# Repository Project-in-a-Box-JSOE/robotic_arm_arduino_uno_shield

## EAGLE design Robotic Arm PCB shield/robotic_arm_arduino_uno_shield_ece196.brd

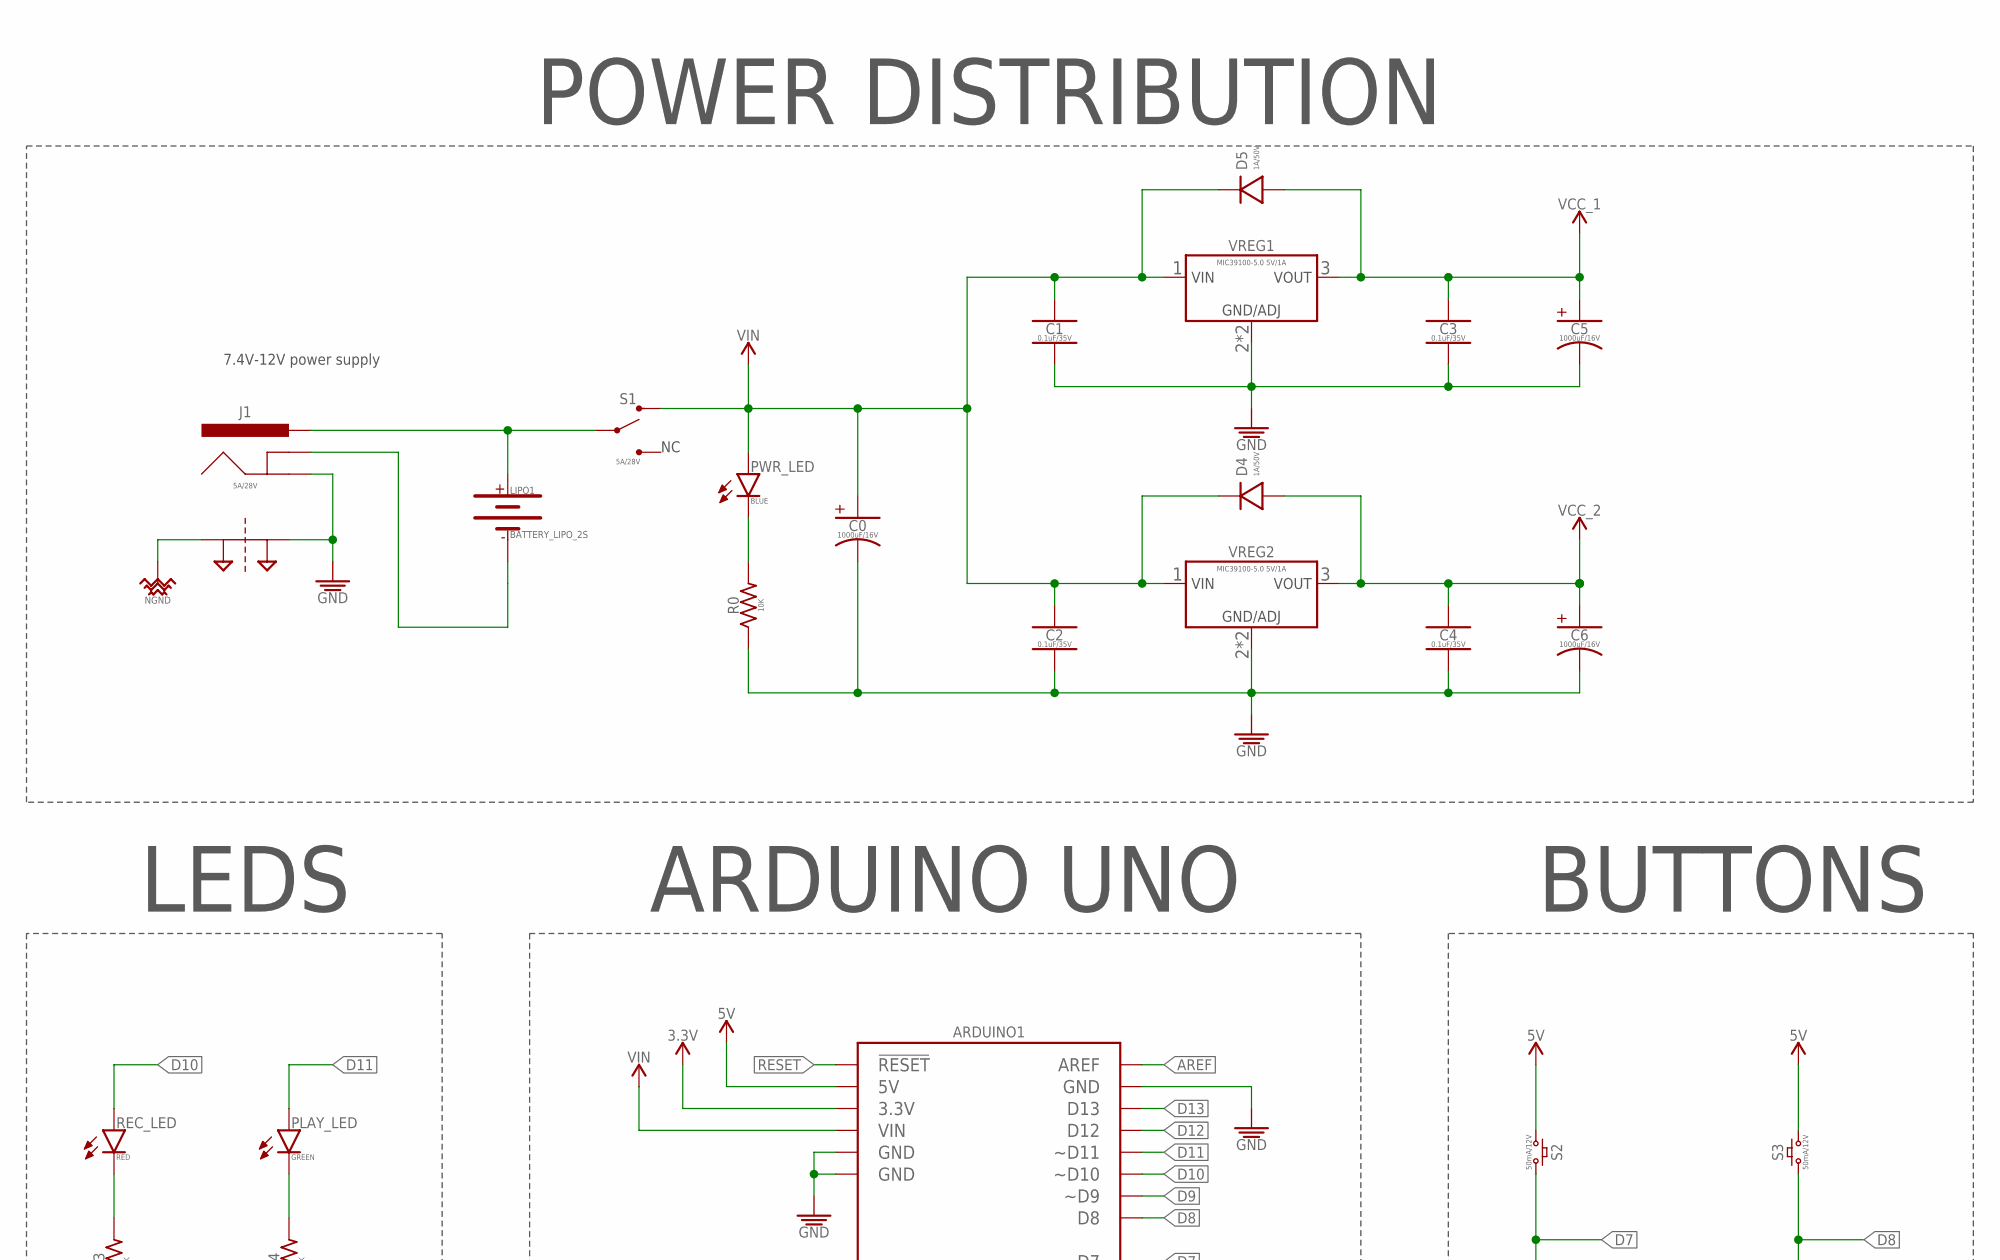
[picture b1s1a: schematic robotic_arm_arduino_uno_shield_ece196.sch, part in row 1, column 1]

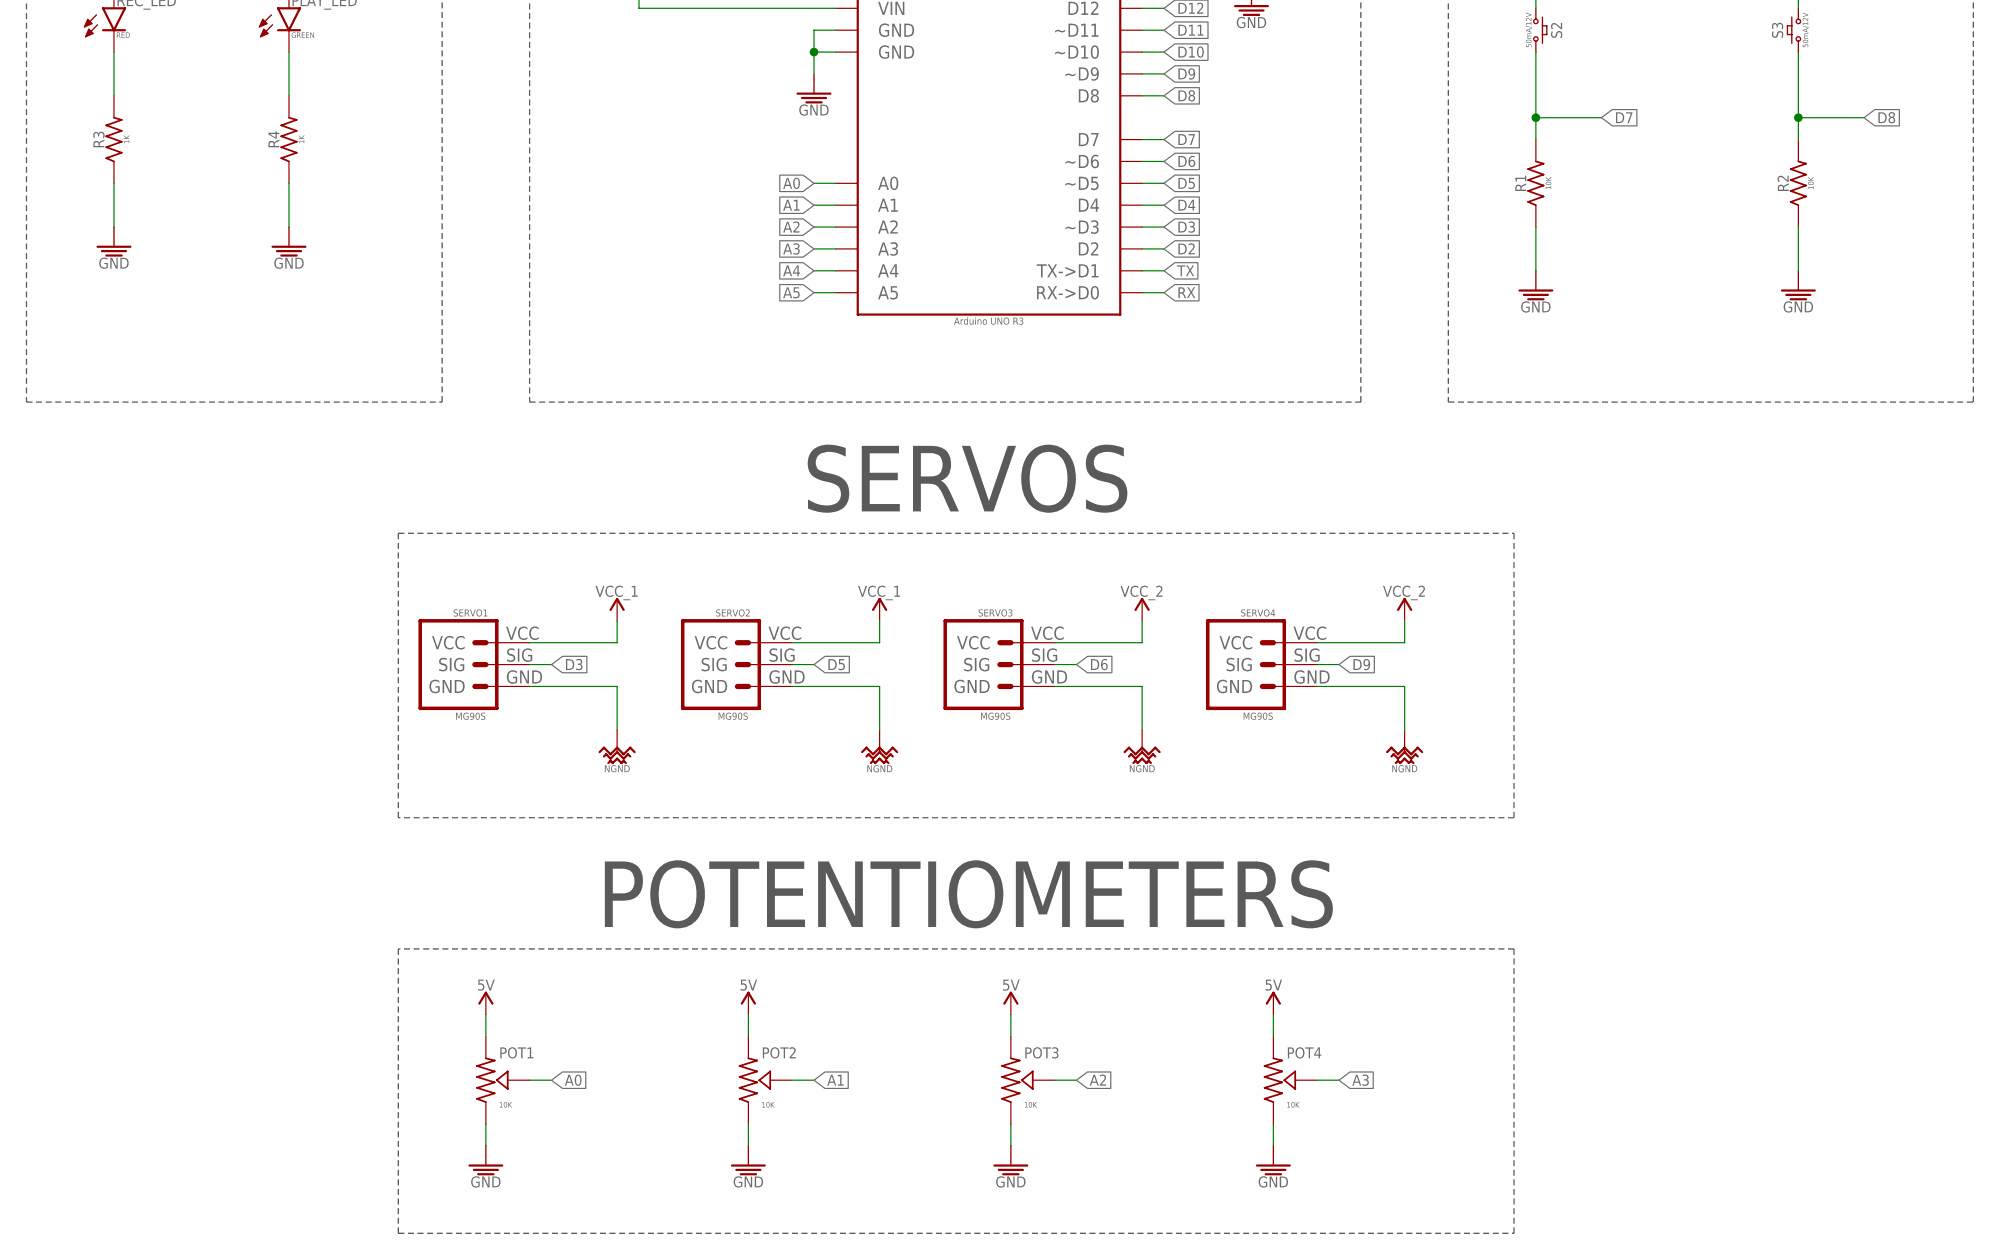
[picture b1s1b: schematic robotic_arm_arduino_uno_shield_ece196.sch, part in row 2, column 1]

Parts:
ARDUINO1: Arduino UNO R3; ARDUINO_UNO_R3_NO-HOLES_NO-AVR-ISP_NO-I2C_NO-NC_NO-IOREF
C0, C5, C6: 1000uF/16V; _AE_PTH_DIA8-LS3.5-H21.50
C1, C2, C3, C4: 0.1uF/35V; CAPC2012X95_SMD-0805
D4, D5: 1A/50V; SODFL3516X170
J1: 5A/28V; POWER_JACK_PTH_ID2.1MM-OD5.5MM
LIPO1: BATTERY_LIPO_2S; DUAL_PTH_PADS
PLAY_LED: GREEN; LEDC2012X120_LED-0805
POT1, POT2, POT3, POT4: 10K; HDRVR3W64P254_1X3_812X254X850B
PWR_LED: BLUE; LEDC2012X120_LED-0805
R0, R1, R2: 10K; RESC2012X60_SMD-0805
R3, R4: 1K; RESC2012X60_SMD-0805
REC_LED: RED; LEDC2012X120_LED-0805
S1: 5A/28V; SW_TOGGLE_SPDT_5A-28V_13L-7W
S2, S3: 50mA/12V; BTN_MOMENTARY_SPST-NO_PTH_L12-W12
SERVO1, SERVO2, SERVO3, SERVO4: MG90S; HDRVR3W64P254_1X3_812X254X850B
SUPPLY14: NET_BRIDGE
VREG1, VREG2: MIC39100-5.0 5V/1A; SOT229P700X180-4

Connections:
3.3V: ARDUINO1.3.3V
5V: ARDUINO1.5V, POT1.CCW, POT2.CCW, POT3.CCW, POT4.CCW, S2.1, S3.3 (2)
+: J1.PWR, LIPO1.+, S1.P
-: J1.GND_BATTERY, LIPO1.-
A0: ARDUINO1.A0, POT1.S
A1: ARDUINO1.A1, POT2.S
A2: ARDUINO1.A2, POT3.S
A3: ARDUINO1.A3, POT4.S
A4: ARDUINO1.A4
A5: ARDUINO1.A5
AREF: ARDUINO1.AREF
D2: ARDUINO1.D2
D3: ARDUINO1.D3 (~D3), SERVO1.SIG
D4: ARDUINO1.D4
D5: ARDUINO1.D5 (~D5), SERVO2.SIG
D6: ARDUINO1.D6 (~D6), SERVO3.SIG
D7: ARDUINO1.D7, R1.2, S2.3 (2)
D8: ARDUINO1.D8, R2.2, S3.1
D9: ARDUINO1.D9 (~D9), SERVO4.SIG
D10: ARDUINO1.D10 (~D10), REC_LED.A
D11: ARDUINO1.D11 (~D11), PLAY_LED.A
D12: ARDUINO1.D12
D13: ARDUINO1.D13
GND: ARDUINO1.GND@1 (GND), ARDUINO1.GND@2 (GND), ARDUINO1.GND@3 (GND), C0.- (K), C1.2, C2.2, C3.2, C4.2, C5.- (K), C6.- (K), J1.GND_JACK, POT1.CW, POT2.CW, POT3.CW, POT4.CW, R0.1, R1.1, R2.1, R3.1, R4.1, SUPPLY14.P$2, VREG1.2 (GND), VREG1.TAB (GND), VREG2.2 (GND), VREG2.TAB (GND)
unnamed: PLAY_LED.K, R4.2
unnamed: R3.2, REC_LED.K
unnamed: PWR_LED.K, R0.2
NGND: SERVO1.GND, SERVO2.GND, SERVO3.GND, SERVO4.GND, SUPPLY14.P$1
RESET: ARDUINO1.RESET@1 (!RESET!)
RX: ARDUINO1.D0 (RX->D0)
TX: ARDUINO1.D1 (TX->D1)
VCC_1: C3.1, C5.+ (A), D5.A, SERVO1.VCC, SERVO2.VCC, VREG1.3 (VO)
VCC_2: C4.1, C6.+ (A), D4.A, SERVO3.VCC, SERVO4.VCC, VREG2.3 (VO)
VIN: ARDUINO1.VIN, C0.+ (A), C1.1, C2.1, D4.K, D5.K, PWR_LED.A, S1.S1, VREG1.1 (VI), VREG2.1 (VI)

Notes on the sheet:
7.4V-12V power supply
SERVOS
LEDS
BUTTONS
ARDUINO UNO
POTENTIOMETERS
POWER DISTRIBUTION

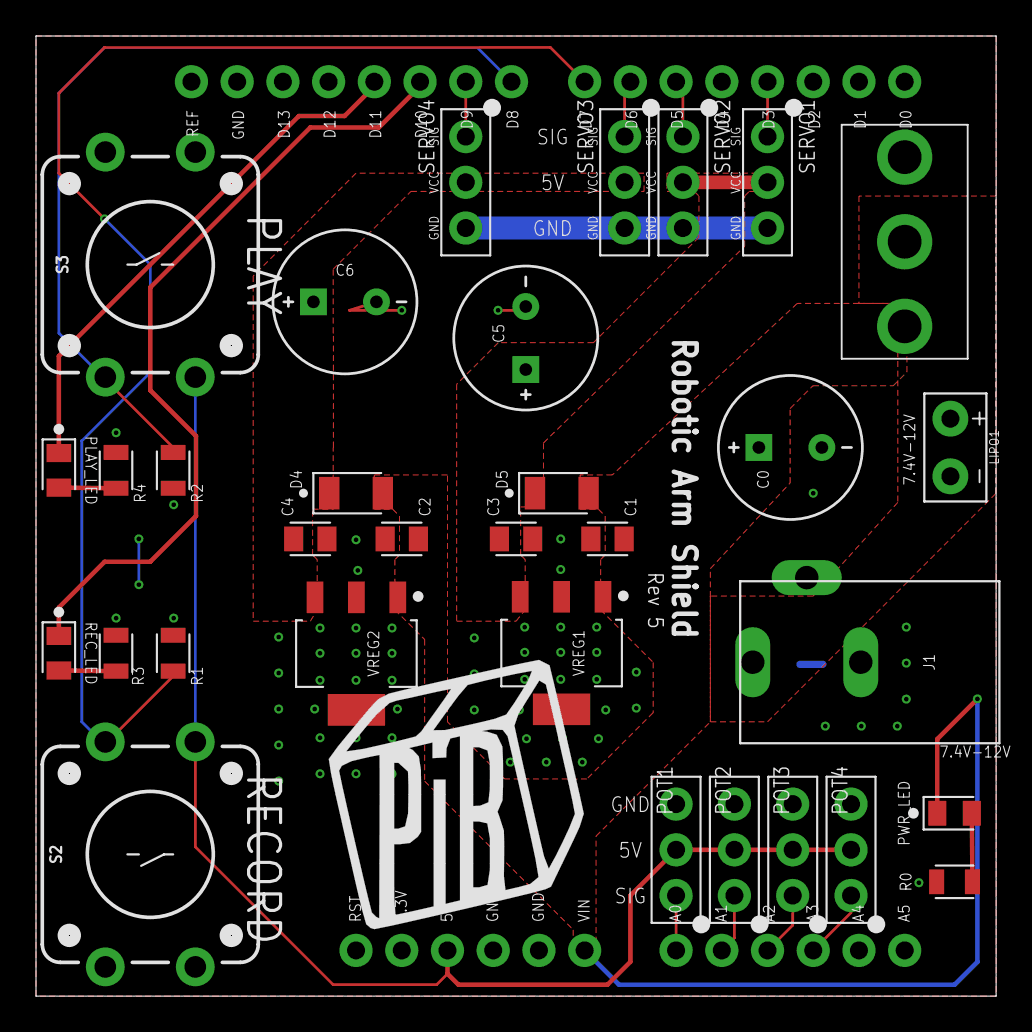
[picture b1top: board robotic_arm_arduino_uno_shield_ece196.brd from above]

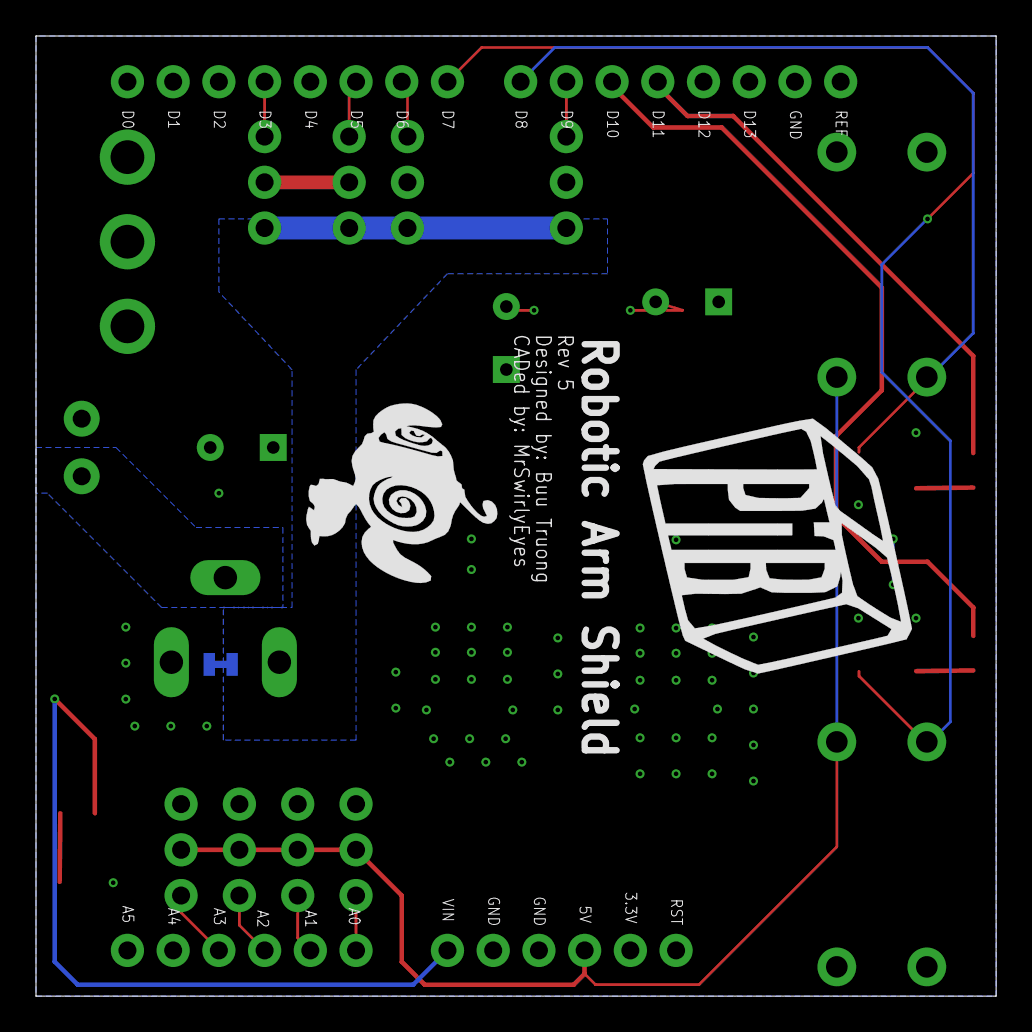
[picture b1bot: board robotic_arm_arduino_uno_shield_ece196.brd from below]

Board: 2 copper layers, 53.3 x 53.3 mm, 37 parts (3 on the bottom side), 23 nets.

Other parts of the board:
U$2: MRSWIRLYEYES-LOGO
U$3, U$4: PIB_LOGO_5MM

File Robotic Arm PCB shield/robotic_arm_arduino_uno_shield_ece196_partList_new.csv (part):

"Part";"Value";"Device";"Package";"Description";"DATASHEET";"DATASHEET_CABLE";"DATASHEET_CONNECTOR";"DIST";"DISTLINK";"DISTLINK_CABLE";"DISTLINK_CONNECTOR";"DISTLINK_CONNECTOR1";"DISTLINK_CONNECTOR2";"DISTPN";"DISTPN_CABLE";"DISTPN_CONNECTOR";"DISTPN_CONNECTOR1";"DISTPN_CONNECTOR2";"DIST_CABLE";"DIST_CONNECTOR";"MFR";"MFR_CABLE";"MFR_CONNECTOR";"MPN";"MPN_CABLE";"MPN_CONNECTOR";"MPN_CONNECTOR1";"MPN_CONNECTOR2";"QTY_CONNECTOR1";"QTY_CONNECTOR2";"VALUE";
"ARDUINO1";"Arduino UNO R3";"ARDUINO_UNO_R3_NO-HOLES_NO-AVR-ISP_NO-I2C_NO-NC_NO-IOREF";"ARDUINO_UNO_R3_NO-HOLES_NO-AVR-ISP_NO-I2C_NO-NC_NO-IOREF";"";"https://media.digikey.com/pdf/Data%20Sheets/Arduino%20PDFs/A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";"http://www.assmann-wsw.com/fileadmin/datasheets/ASS_7066_CA.pdf";"http://www.sullinscorp.com/drawings/77____C___S___N-OMIT,_M500,_STRAIGHT,_C10436.pdf";"Digikey";"https://www.digikey.com/products/en?keywords=1050-1024-ND";"https://www.digikey.com/products/en?keywords=AE1462-ND";"";"https://www.digikey.com/products/en?keywords=S1012E-06-ND";"https://www.digikey.com/products/en?keywords=PEC08SAAN";"1050-1024-ND";"AE1462-ND";"";"S1012E-06-ND";"S1012E-08-ND";"Digikey";"Digikey";"Arduino";"Assmann WSW Components";"Sullins Connector Solutions";"A000066";"AK672/2-1";"";"PEC06SAAN";"PEC08SAAN";"2";"2";"Arduino UNO R3";
"C0";"1000uF/16V";"1000UF-POLARIZED_PTH_16V-20%";"_AE_PTH_DIA8-LS3.5-H21.50";"";"http://www.chemi-con.co.jp/cgi-bin/CAT_DB/SEARCH/cat_db_al.c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";"";"";"Digikey";"https://www.digikey.com/products/en?keywords=565-3567-ND";"";"";"";"";"565-3567-ND";"";"";"";"";"";"";"United Chemi-Con";"";"";"EKZM160ELL102MH20D";"";"";"";"";"";"";"1000uF/16V";
"C1";"0.1uF/35V";"0.1UF_SMD-0805_35V-10%";"CAPC2012X95_SMD-0805";"";"http://ds.yuden.co.jp/TYCOMPAS/ut/detail.do?productNo=GMK212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";"";"";"Digikey";"https://www.digikey.com/products/en?keywords=587-3364-1-ND";"";"";"";"";"587-3364-1-ND";"";"";"";"";"";"";"Taiyo Yuden";"";"";"GMK212BJ104KGHT";"";"";"";"";"";"";"0.1uF/35V";
"C2";"0.1uF/35V";"0.1UF_SMD-0805_35V-10%";"CAPC2012X95_SMD-0805";"";"http://ds.yuden.co.jp/TYCOMPAS/ut/detail.do?productNo=GMK212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";"";"";"Digikey";"https://www.digikey.com/products/en?keywords=587-3364-1-ND";"";"";"";"";"587-3364-1-ND";"";"";"";"";"";"";"Taiyo Yuden";"";"";"GMK212BJ104KGHT";"";"";"";"";"";"";"0.1uF/35V";
"C3";"0.1uF/35V";"0.1UF_SMD-0805_35V-10%";"CAPC2012X95_SMD-0805";"";"http://ds.yuden.co.jp/TYCOMPAS/ut/detail.do?productNo=GMK212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";"";"";"Digikey";"https://www.digikey.com/products/en?keywords=587-3364-1-ND";"";"";"";"";"587-3364-1-ND";"";"";"";"";"";"";"Taiyo Yuden";"";"";"GMK212BJ104KGHT";"";"";"";"";"";"";"0.1uF/35V";
"C4";"0.1uF/35V";"0.1UF_SMD-0805_35V-10%";"CAPC2012X95_SMD-0805";"";"http://ds.yuden.co.jp/TYCOMPAS/ut/detail.do?productNo=GMK212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";"";"";"Digikey";"https://www.digikey.com/products/en?keywords=587-3364-1-ND";"";"";"";"";"587-3364-1-ND";"";"";"";"";"";"";"Taiyo Yuden";"";"";"GMK212BJ104KGHT";"";"";"";"";"";"";"0.1uF/35V";
"C5";"1000uF/16V";"1000UF-POLARIZED_PTH_16V-20%";"_AE_PTH_DIA8-LS3.5-H21.50";"";"http://www.chemi-con.co.jp/cgi-bin/CAT_DB/SEARCH/cat_db_al.c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";"";"";"Digikey";"https://www.digikey.com/products/en?keywords=565-3567-ND";"";"";"";"";"565-3567-ND";"";"";"";"";"";"";"United Chemi-Con";"";"";"EKZM160ELL102MH20D";"";"";"";"";"";"";"1000uF/16V";
"C6";"1000uF/16V";"1000UF-POLARIZED_PTH_16V-20%";"_AE_PTH_DIA8-LS3.5-H21.50";"";"http://www.chemi-con.co.jp/cgi-bin/CAT_DB/SEARCH/cat_db_al.c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";"";"";"Digikey";"https://www.digikey.com/products/en?keywords=565-3567-ND";"";"";"";"";"565-3567-ND";"";"";"";"";"";"";"United Chemi-Con";"";"";"EKZM160ELL102MH20D";"";"";"";"";"";"";"1000uF/16V";
"D4";"1A/50V";"DIODE_GENERAL-PURPOSE_SMD_GP_1A-50V";"SODFL3516X170";"";"http://www.comchiptech.com/cms/UserFiles/CGRKM4001-HF%20Thru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";"";"";"Digikey";"https://www.digikey.com/products/en?keywords=641-1511-1-ND";"";"";"";"";"641-1511-1-ND";"";"";"";"";"";"";"Comchip Technology";"";"";"CGRKM4001-HF";"";"";"";"";"";"";"1A/50V";
"D5";"1A/50V";"DIODE_GENERAL-PURPOSE_SMD_GP_1A-50V";"SODFL3516X170";"";"http://www.comchiptech.com/cms/UserFiles/CGRKM4001-HF%20Thru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";"";"";"Digikey";"https://www.digikey.com/products/en?keywords=641-1511-1-ND";"";"";"";"";"641-1511-1-ND";"";"";"";"";"";"";"Comchip Technology";"";"";"CGRKM4001-HF";"";"";"";"";"";"";"1A/50V";
"J1";"5A/28V";"POWER_JACK-BARREL_ID2.1MM-OD5.5MM_PTH_ID2.1MM-OD5.5MM";"POWER_JACK_PTH_ID2.1MM-OD5.5MM";"";"https://www.cui.com/product/resource/pj-102a.pdf";"";"";"Digikey";"https://www.digikey.com/products/en?keywords=CP-102A-ND";"";"";"";"";"CP-102A-ND";"";"";"";"";"";"";"CUI Inc.";"";"";"PJ-102A";"";"";"";"";"";"";"5A/28V";
"LIPO1";"BATTERY_LIPO_2S";"BATTERY_LIPO_2S";"DUAL_PTH_PADS";"";"";"";"";"";"";"";"";"";"";"";"";"";"";"";"";"";"";"";"";"";"";"";"";"";"";"";"";
"PLAY_LED";"GREEN";"LED_SMD-0805_DISCRETE_GREEN";"LEDC2012X120_LED-0805";"";"http://optoelectronics.liteon.com/upload/download/DS22-2000-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";"";"";"Digikey";"https://www.digikey.com/products/en?keywords=160-1414-1-ND";"";"";"";"";"160-1414-1-ND";"";"";"";"";"";"";"Lite-On Inc.";"";"";"LTST-C170KGKT";"";"";"";"";"";"";"GREEN";
"POT1";"10K";"POTENTIOMETER_CONNECTOR_PTH_VERT_FEMALE_2.54MM";"HDRVR3W64P254_1X3_812X254X850B";"";"http://www.ttelectronics.com/sites/default/files/download-fi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";"";"https://drawings-pdf.s3.amazonaws.com/10492.pdf";"Digikey";"https://www.digikey.com/products/en?keywords=987-1715-ND";"";"https://www.digikey.com/products/en?keywords=PPTC031LFBN-RC";"";"";"987-1715-ND";"";"S7001-ND";"";"";"";"Digikey";"TT Electronics/BI";"";"Sullins Connector Solutions";"P160KN2-0QA25B10K";"";"PPTC031LFBN-RC";"";"";"";"";"10K";
"POT2";"10K";"POTENTIOMETER_CONNECTOR_PTH_VERT_FEMALE_2.54MM";"HDRVR3W64P254_1X3_812X254X850B";"";"http://www.ttelectronics.com/sites/default/files/download-fi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";"";"https://drawings-pdf.s3.amazonaws.com/10492.pdf";"Digikey";"https://www.digikey.com/products/en?keywords=987-1715-ND";"";"https://www.digikey.com/products/en?keywords=PPTC031LFBN-RC";"";"";"987-1715-ND";"";"S7001-ND";"";"";"";"Digikey";"TT Electronics/BI";"";"Sullins Connector Solutions";"P160KN2-0QA25B10K";"";"PPTC031LFBN-RC";"";"";"";"";"10K";
"POT3";"10K";"POTENTIOMETER_CONNECTOR_PTH_VERT_FEMALE_2.54MM";"HDRVR3W64P254_1X3_812X254X850B";"";"http://www.ttelectronics.com/sites/default/files/download-fi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";"";"https://drawings-pdf.s3.amazonaws.com/10492.pdf";"Digikey";"https://www.digikey.com/products/en?keywords=987-1715-ND";"";"https://www.digikey.com/products/en?keywords=PPTC031LFBN-RC";"";"";"987-1715-ND";"";"S7001-ND";"";"";"";"Digikey";"TT Electronics/BI";"";"Sullins Connector Solutions";"P160KN2-0QA25B10K";"";"PPTC031LFBN-RC";"";"";"";"";"10K";
"POT4";"10K";"POTENTIOMETER_CONNECTOR_PTH_VERT_FEMALE_2.54MM";"HDRVR3W64P254_1X3_812X254X850B";"";"http://www.ttelectronics.com/sites/default/files/download-fi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";"";"https://drawings-pdf.s3.amazonaws.com/10492.pdf";"Digikey";"https://www.digikey.com/products/en?keywords=987-1715-ND";"";"https://www.digikey.com/products/en?keywords=PPTC031LFBN-RC";"";"";"987-1715-ND";"";"S7001-ND";"";"";"";"Digikey";"TT Electronics/BI";"";"Sullins Connector Solutions";"P160KN2-0QA25B10K";"";"PPTC031LFBN-RC";"";"";"";"";"10K";
"PWR_LED";"BLUE";"LED_SMD-0805_DISCRETE_BLUE";"LEDC2012X120_LED-0805";"";"http://optoelectronics.liteon.com/upload/download/DS-22-99-0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";"";"";"Digikey";"https://www.digikey.com/products/en?keywords=160-1579-1-ND";"";"";"";"";"160-1579-1-ND";"";"";"";"";"";"";"Lite-On Inc.";"";"";"LTST-C170TBKT";"";"";"";"";"";"";"BLUE";
"R0";"10K";"10KΩ_SMD-0805_1/8W-5%";"RESC2012X60_SMD-0805";"";"http://www.yageo.com/documents/recent/PYu-RC_Group_51_RoHS_L_9.pdf";"";"";"Digikey";"https://www.digikey.com/products/en?keywords=311-10KARCT-ND";"";"";"";"";"311-10KARCT-ND";"";"";"";"";"";"";"Yageo";"";"";"RC0805JR-0710KL";"";"";"";"";"";"";"10K";
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
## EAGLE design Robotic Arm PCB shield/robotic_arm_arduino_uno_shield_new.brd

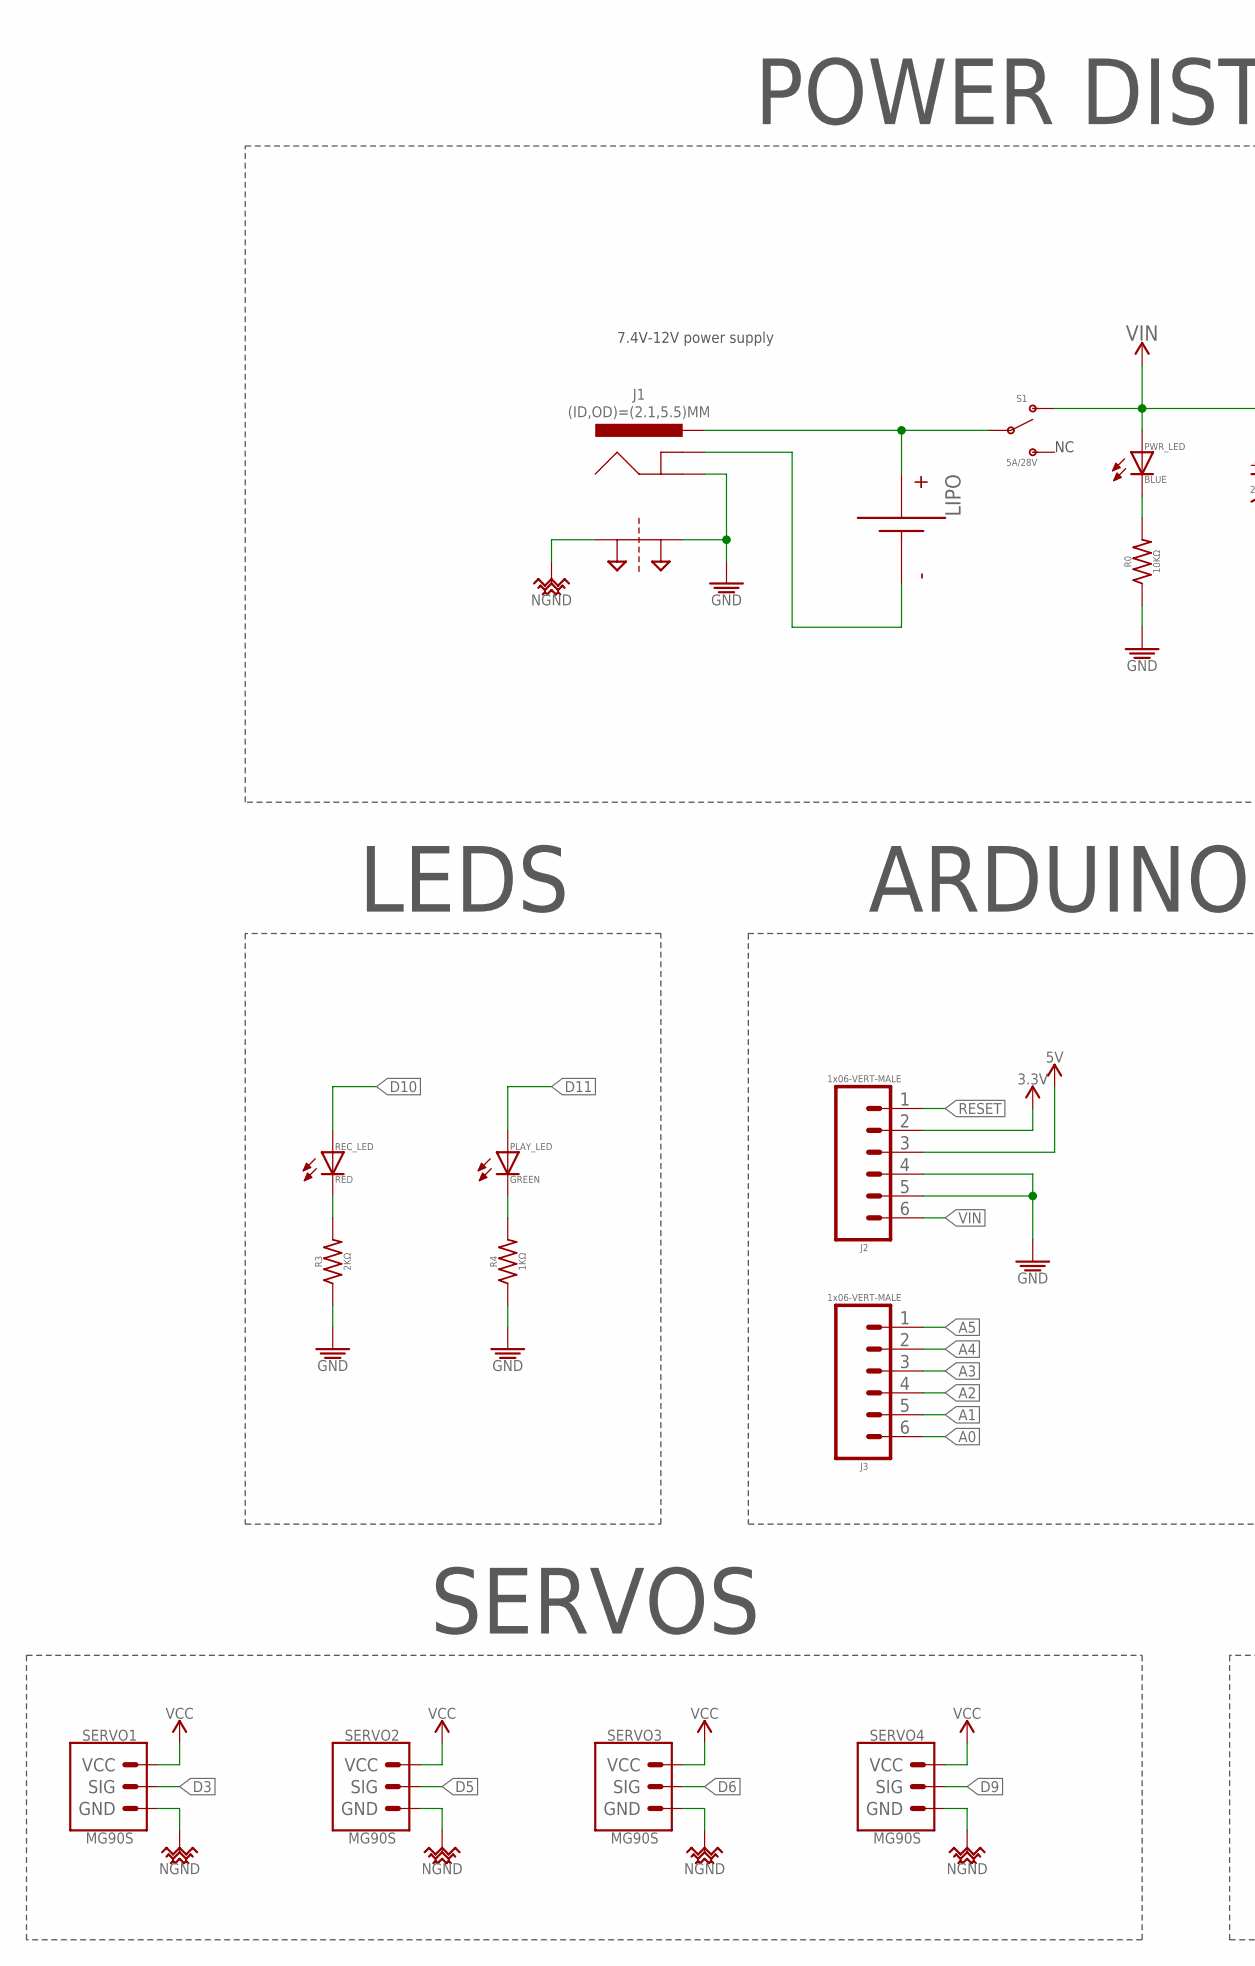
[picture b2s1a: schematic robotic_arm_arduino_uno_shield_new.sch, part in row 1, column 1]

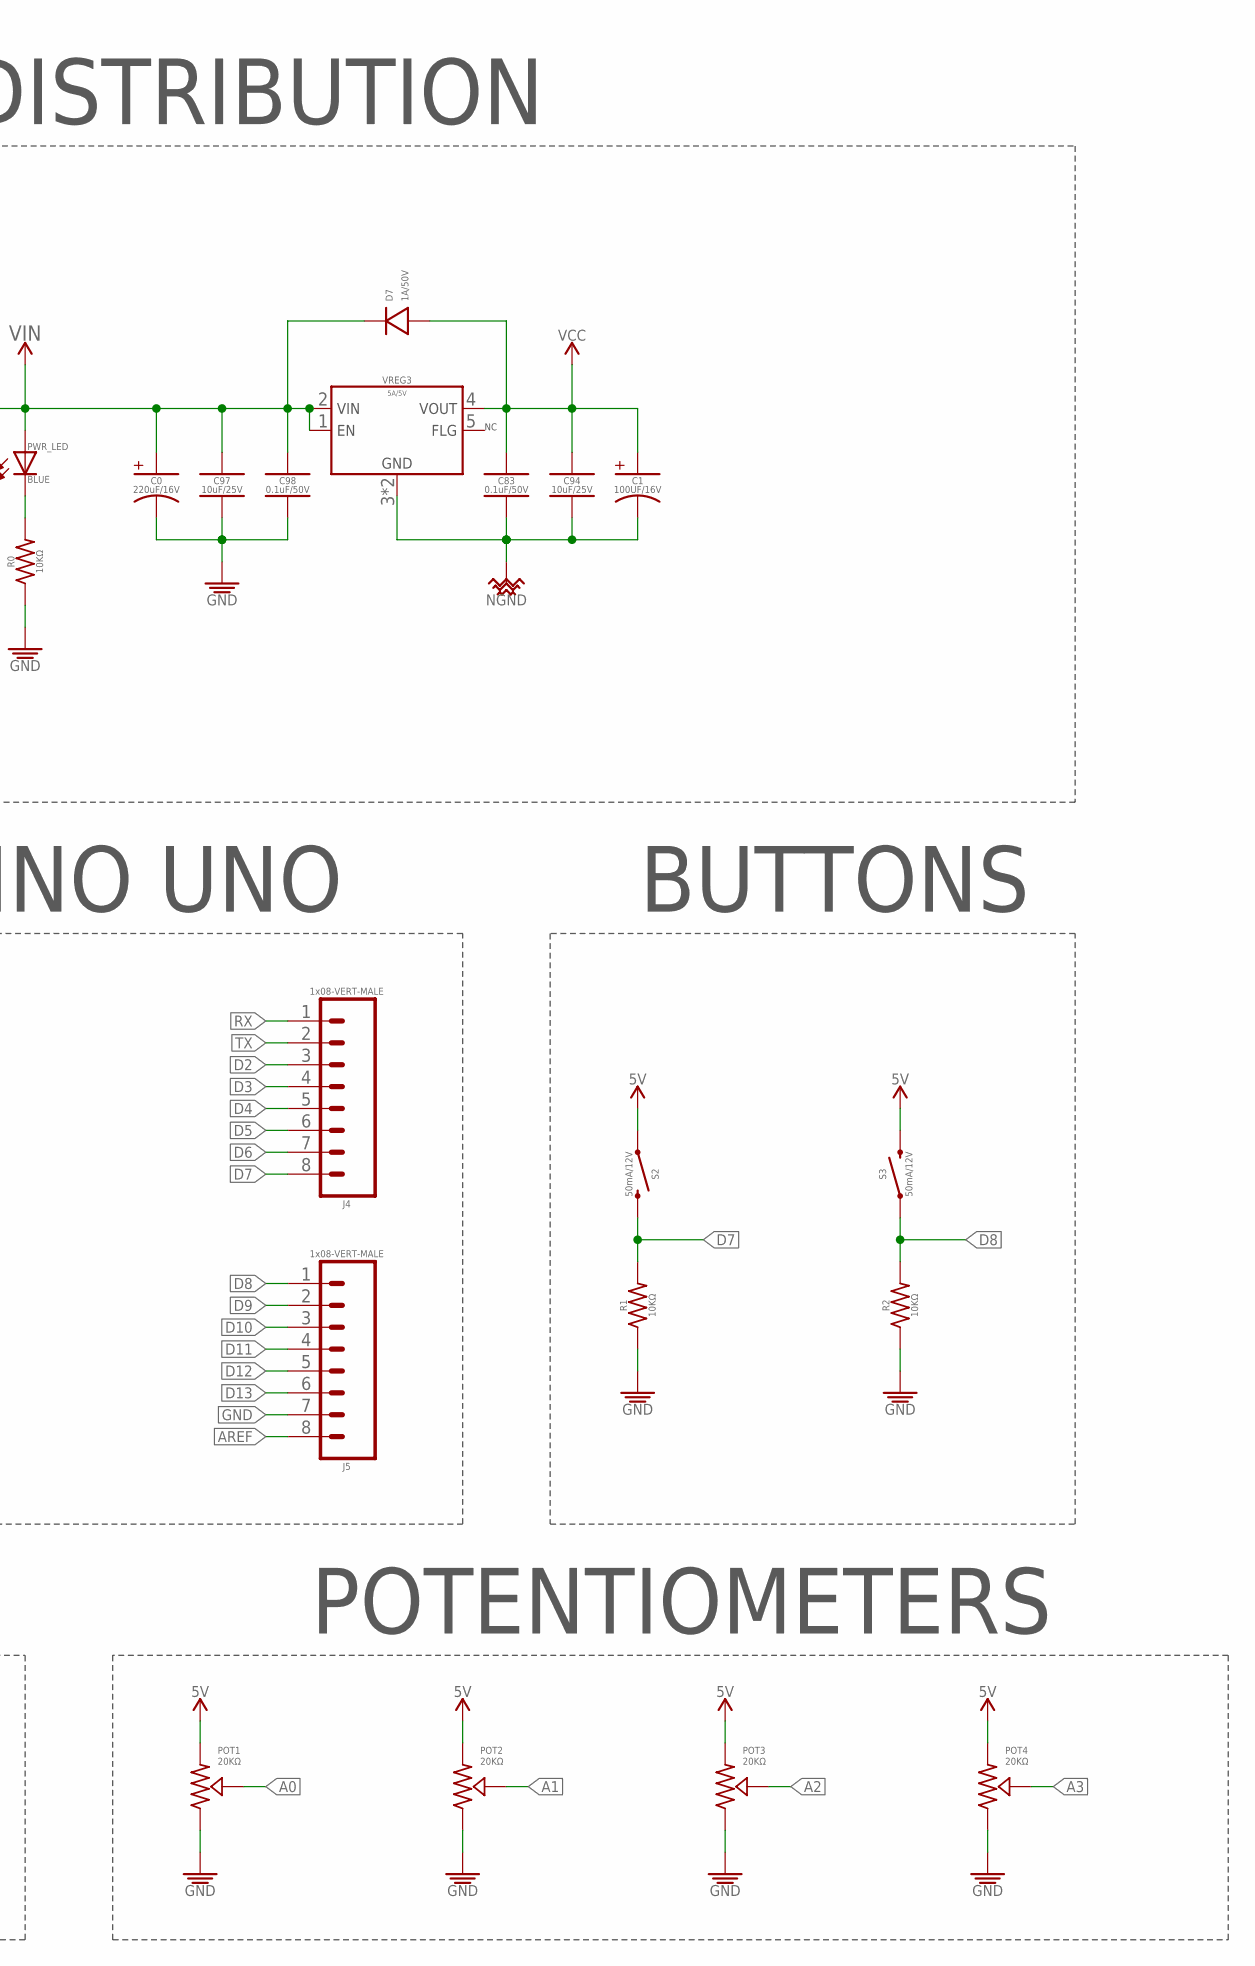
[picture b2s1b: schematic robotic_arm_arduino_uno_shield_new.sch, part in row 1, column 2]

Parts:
C0: 220uF/16V; CAP_POL_SMD_L6.6-W6.6
C1: 100UF/16V; CAP_POL_SMD_L6.6-W6.6
C83, C98: 0.1uF/50V; CAP_CER_SMD-805
C94, C97: 10uF/25V; CAP_CER_SMD-805
D7: 1A/50V; DIODE_SMD_1A-50V-SOD123F
J1: (ID,OD)=(2.1,5.5)MM; POWER_JACK_SLOT_ID2.1MM-OD5.5MM
J2, J3: 1x06-VERT-MALE; 1X06-VERT-MALE
J4, J5: 1x08-VERT-MALE; 1X08-VERT-MALE
LIPO: BATTERYPTH_HOLES; DUAL_PTH_PADS
PLAY_LED: GREEN; LED_SMD-805_
POT1, POT2, POT3, POT4: 20KΩ; CONNECTOR_POTENTIOMETER_NO-MARKINGS_FEMALE-HEADER
PWR_LED: BLUE; LED_SMD-805_
R0, R1, R2: 10KΩ; RESISTOR_SMD-805
R3: 2KΩ; RESISTOR_SMD-805
R4: 1KΩ; RESISTOR_SMD-805
REC_LED: RED; LED_SMD-805_
S1: 5A/28V; SW-SLIDE_SPDT_5A-28V_13L-7W
S2, S3: 50mA/12V; SPST-PTH-12MM
SERVO1, SERVO2, SERVO3, SERVO4: MG90S; CONNECTOR_SERVO_NO-MARKINGS
SUPPLY14: 2PT_GND_TIE
VREG3: 5A/5V; TO-263-5

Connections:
3.3V: J2.2
5V: J2.3, POT1.CCW, POT2.CCW, POT3.CCW, POT4.CCW, S2.1, S3.3 (2)
+: J1.PWR, LIPO.+, S1.P$2
-: J1.GND@2 (GND), LIPO.- (N)
A0: J3.6, POT1.S
A1: J3.5, POT2.S
A2: J3.4, POT3.S
A3: J3.3, POT4.S
A4: J3.2
A5: J3.1
AREF: J5.8
D2: J4.3
D3: J4.4, SERVO1.1 (SIG)
D4: J4.5
D5: J4.6, SERVO2.1 (SIG)
D6: J4.7, SERVO3.1 (SIG)
D7: J4.8, R1.2, S2.3 (2)
D8: J5.1, R2.2, S3.1
D9: J5.2, SERVO4.1 (SIG)
D10: J5.3, REC_LED.A
D11: J5.4, PLAY_LED.A
D12: J5.5
D13: J5.6
GND: C0.K, C97.2, C98.2, J1.GND@1 (GND), J2.4, J2.5, J5.7, POT1.CW, POT2.CW, POT3.CW, POT4.CW, R0.1, R1.1, R2.1, R3.1, R4.1, SUPPLY14.P$2
unnamed: PLAY_LED.K, R4.2
unnamed: R3.2, REC_LED.K
unnamed: PWR_LED.K, R0.2
NGND: C1.K, C83.2, C94.2, SERVO1.3 (GND), SERVO2.3 (GND), SERVO3.3 (GND), SERVO4.3 (GND), SUPPLY14.P$1, VREG3.3 (GND), VREG3.TAB (GND)
RESET: J2.1
RX: J4.1
TX: J4.2
VCC: C1.A, C83.1, C94.1, D7.A, SERVO1.2 (VCC), SERVO2.2 (VCC), SERVO3.2 (VCC), SERVO4.2 (VCC), VREG3.4 (VOUT)
VIN: C0.A, C97.1, C98.1, D7.K, J2.6, PWR_LED.A, S1.P$1 (S1), VREG3.1 (EN), VREG3.2 (VIN)

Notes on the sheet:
7.4V-12V power supply
SERVOS
LEDS
BUTTONS
ARDUINO UNO
POTENTIOMETERS
POWER DISTRIBUTION

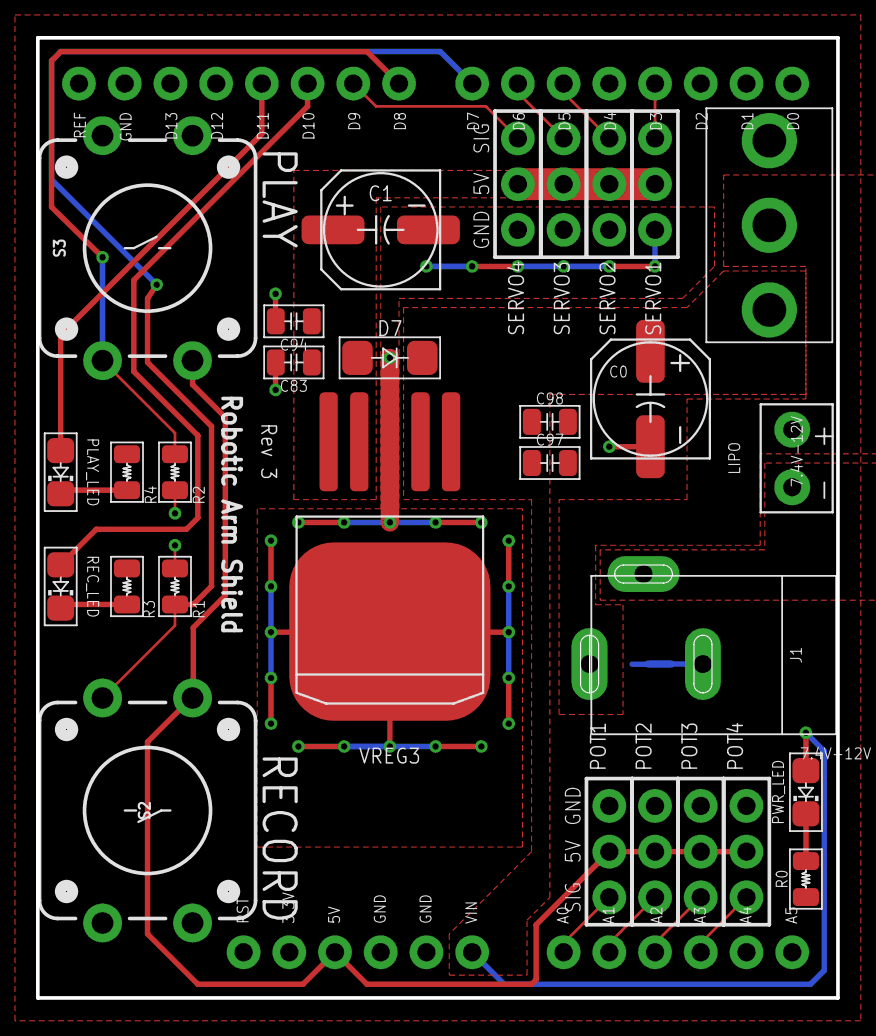
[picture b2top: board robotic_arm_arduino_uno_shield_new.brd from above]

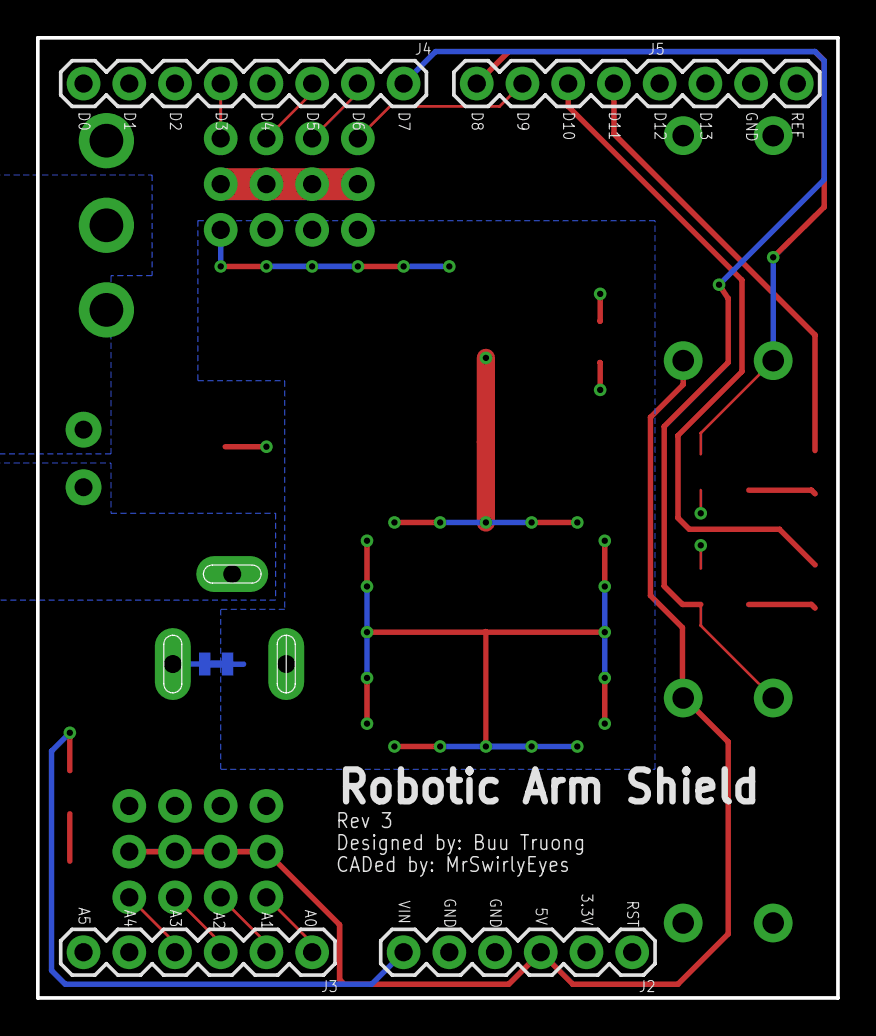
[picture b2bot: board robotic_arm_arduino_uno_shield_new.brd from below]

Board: 2 copper layers, 44.5 x 53.3 mm, 34 parts (5 on the bottom side), 22 nets.

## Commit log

2017-08-01 Added Buus Robotic Arm Arduino Uno Shield
2017-08-01 Adjusted some of the traces
2017-08-01 Adjusted last VIN trace
2017-08-02 Final version. Sending to fab
2017-08-02 Changed out switch. Adjusted traces accordingly
2017-08-02 Small adjusted traces before fab
2017-08-29 Rev 2. Changed pad sizes of 805 SMD components.
2017-09-01 Added switch object parameters for power switch and PLAY,RECORD buttons. Added potentiometer from digikey to POT object. Added Servo from Amazon to SERVO object MG90S
2017-09-01 Rev 2. Modified board and schematic for new parts
2017-09-13 Rev 3: Complete revamp. Replaced the (2) 1A/5V VREGs for (1) 5A/5V VREG
2017-09-13 Rev 3: Adjusted placement of textual elements
2017-09-14 Updated some of the devices with appropriate ATTRIBUTES
2017-09-14 Changed potentiometer because it had the wrong DISTLINK
2018-04-08 Add gitignore. Rename robotic arm schematic to be the new version
2018-04-08 Add ECE196 board - which was a previous revision.
2018-04-08 Fix inconsistency
2018-04-08 Rev 3: ECE 196 board. Add PiB logo.
2018-04-09 Updated ECE196 board. Made a bit smaller
2018-04-09 Small corrections.
2018-04-09 Rev 4: Fixed error not connecting analog pins. Ready for fab.
2018-04-09 Updated attributes of tactile button
2018-07-06 everything except representation
2018-07-06 everything
2018-09-04 Rev 5: Add 1000uF capacitors for potential performance boost by reducing any ripple. Add tons of vias by voltage regulators to help with heat dissipation. Update all components to newest libraries.
2018-09-04 P3 part list updated
2018-09-05 new and better part list

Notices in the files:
parts and their libraries:
SparkFun-PowerSymbols: Licensing: Creative Commons ShareAlike 4.0 International - https://creativecommons.org/licenses/by-sa/4.0
